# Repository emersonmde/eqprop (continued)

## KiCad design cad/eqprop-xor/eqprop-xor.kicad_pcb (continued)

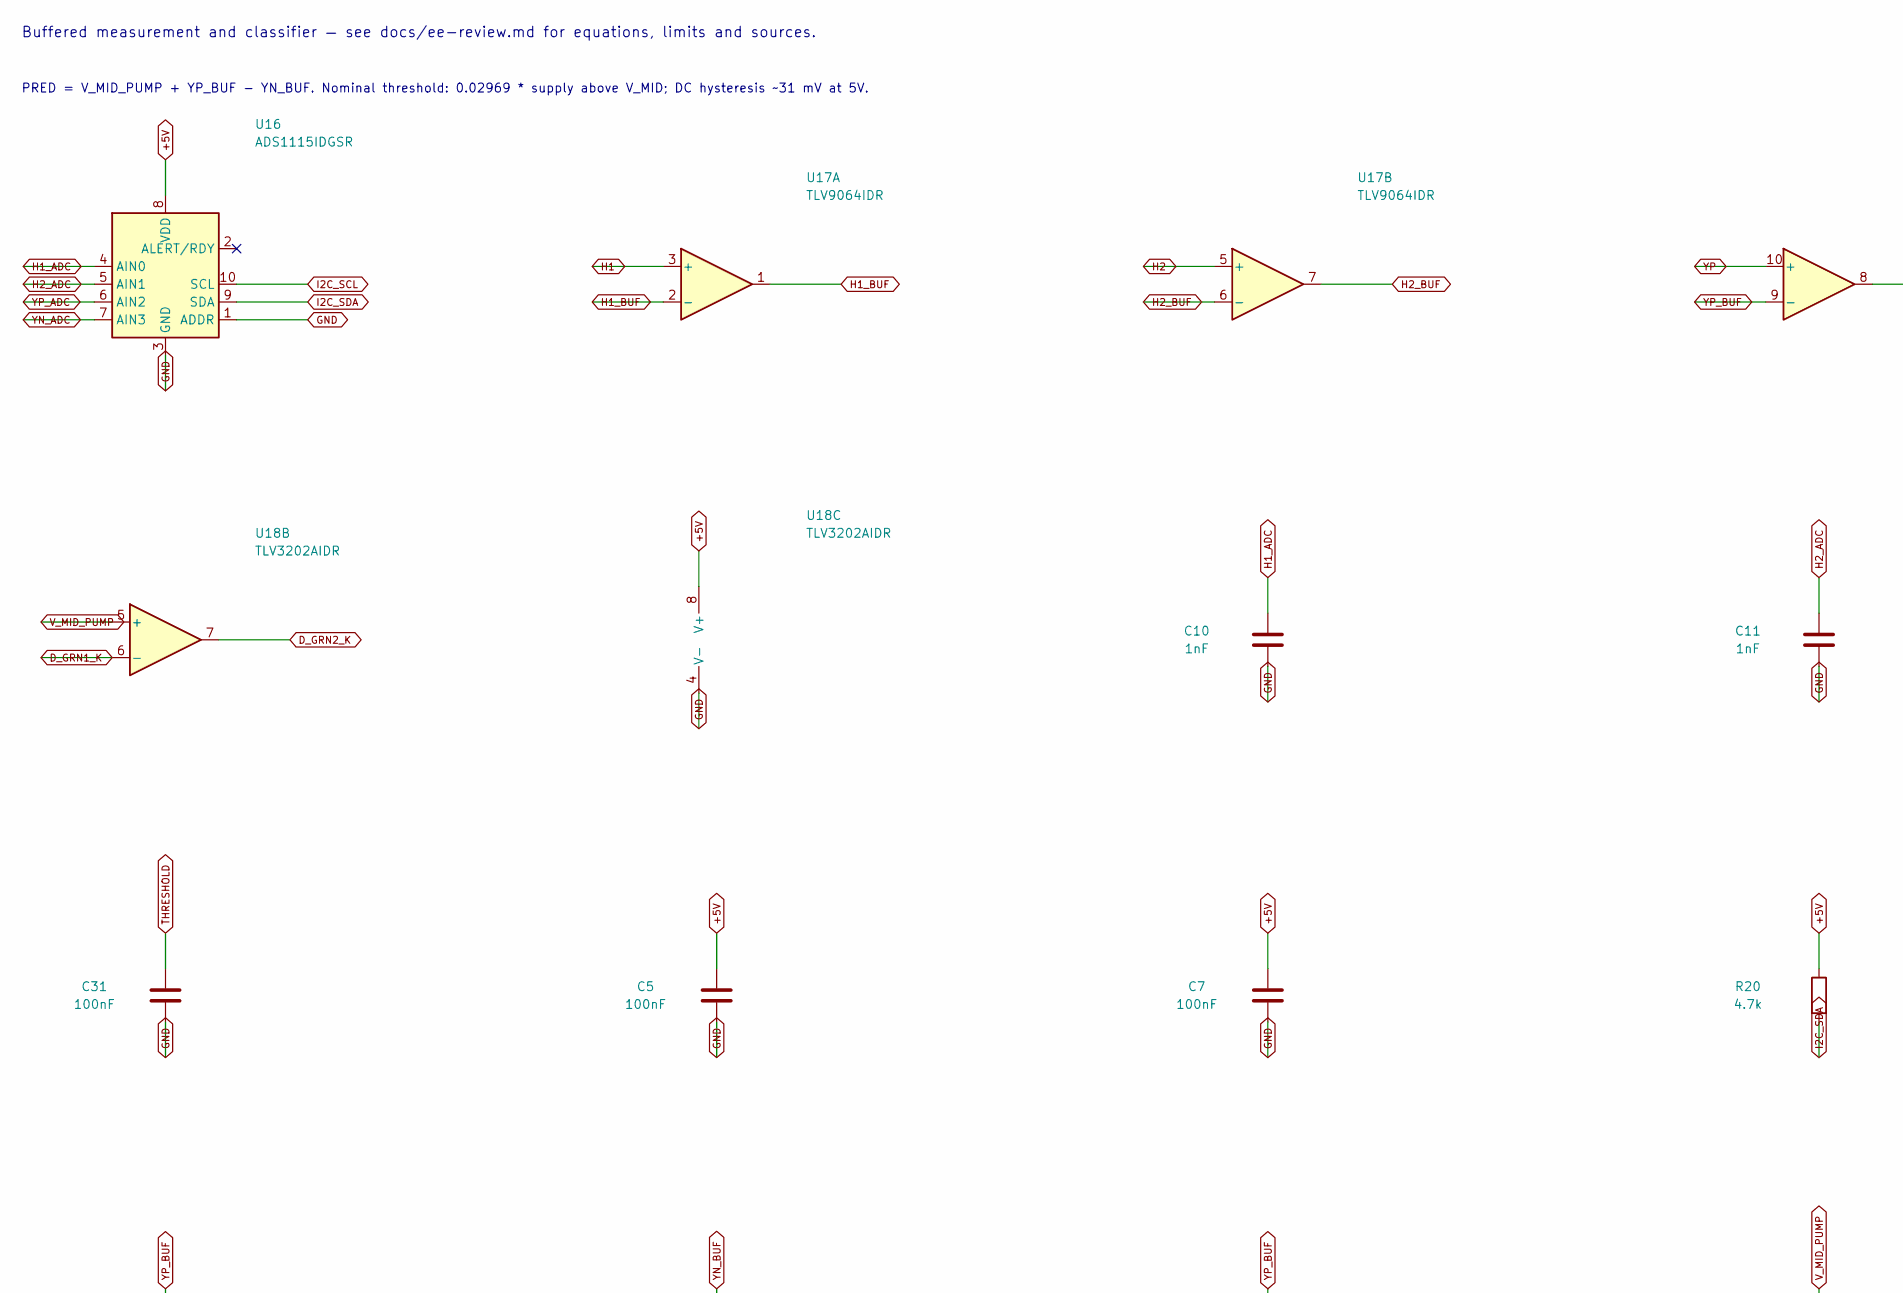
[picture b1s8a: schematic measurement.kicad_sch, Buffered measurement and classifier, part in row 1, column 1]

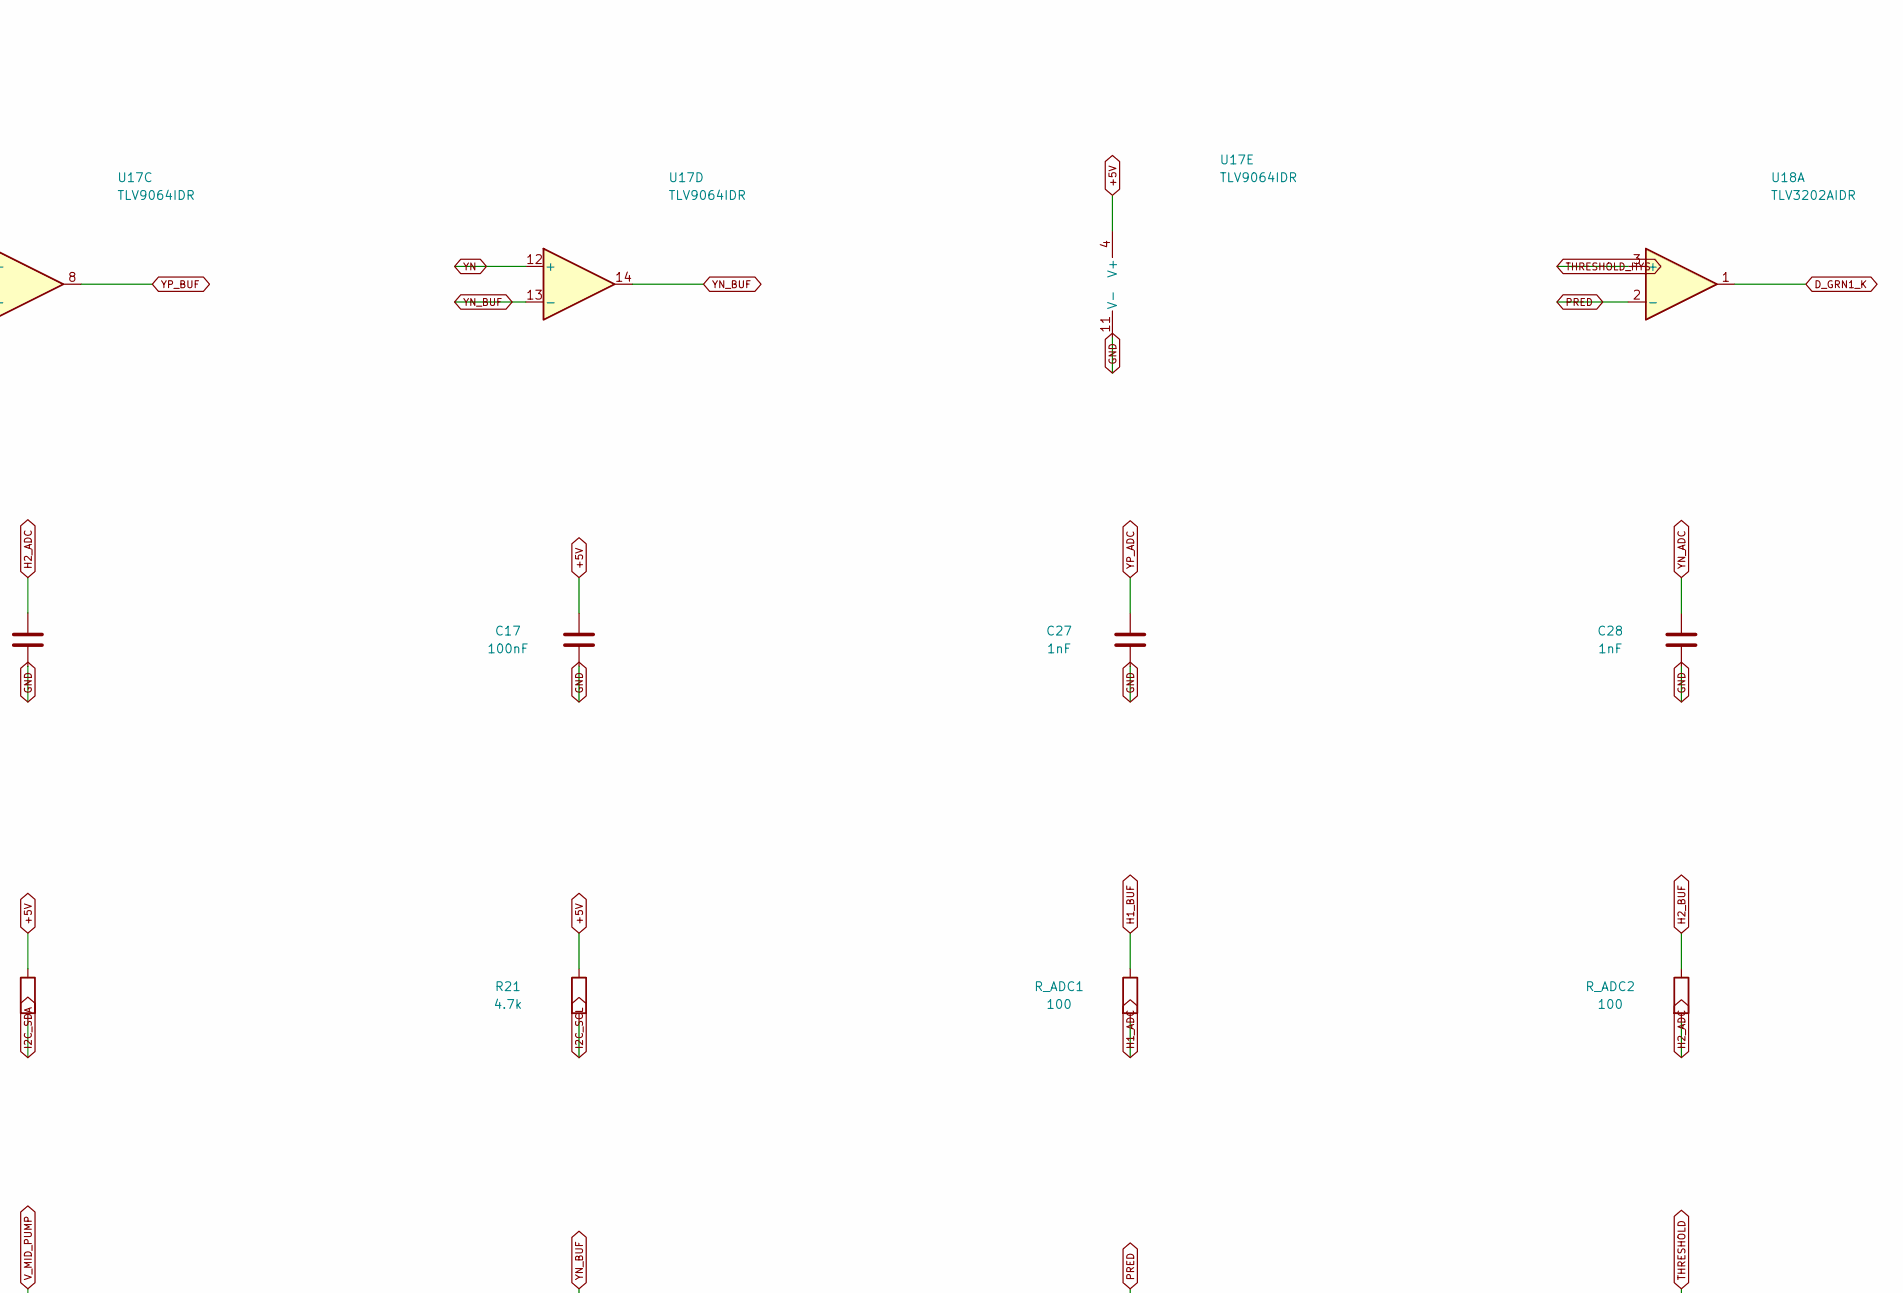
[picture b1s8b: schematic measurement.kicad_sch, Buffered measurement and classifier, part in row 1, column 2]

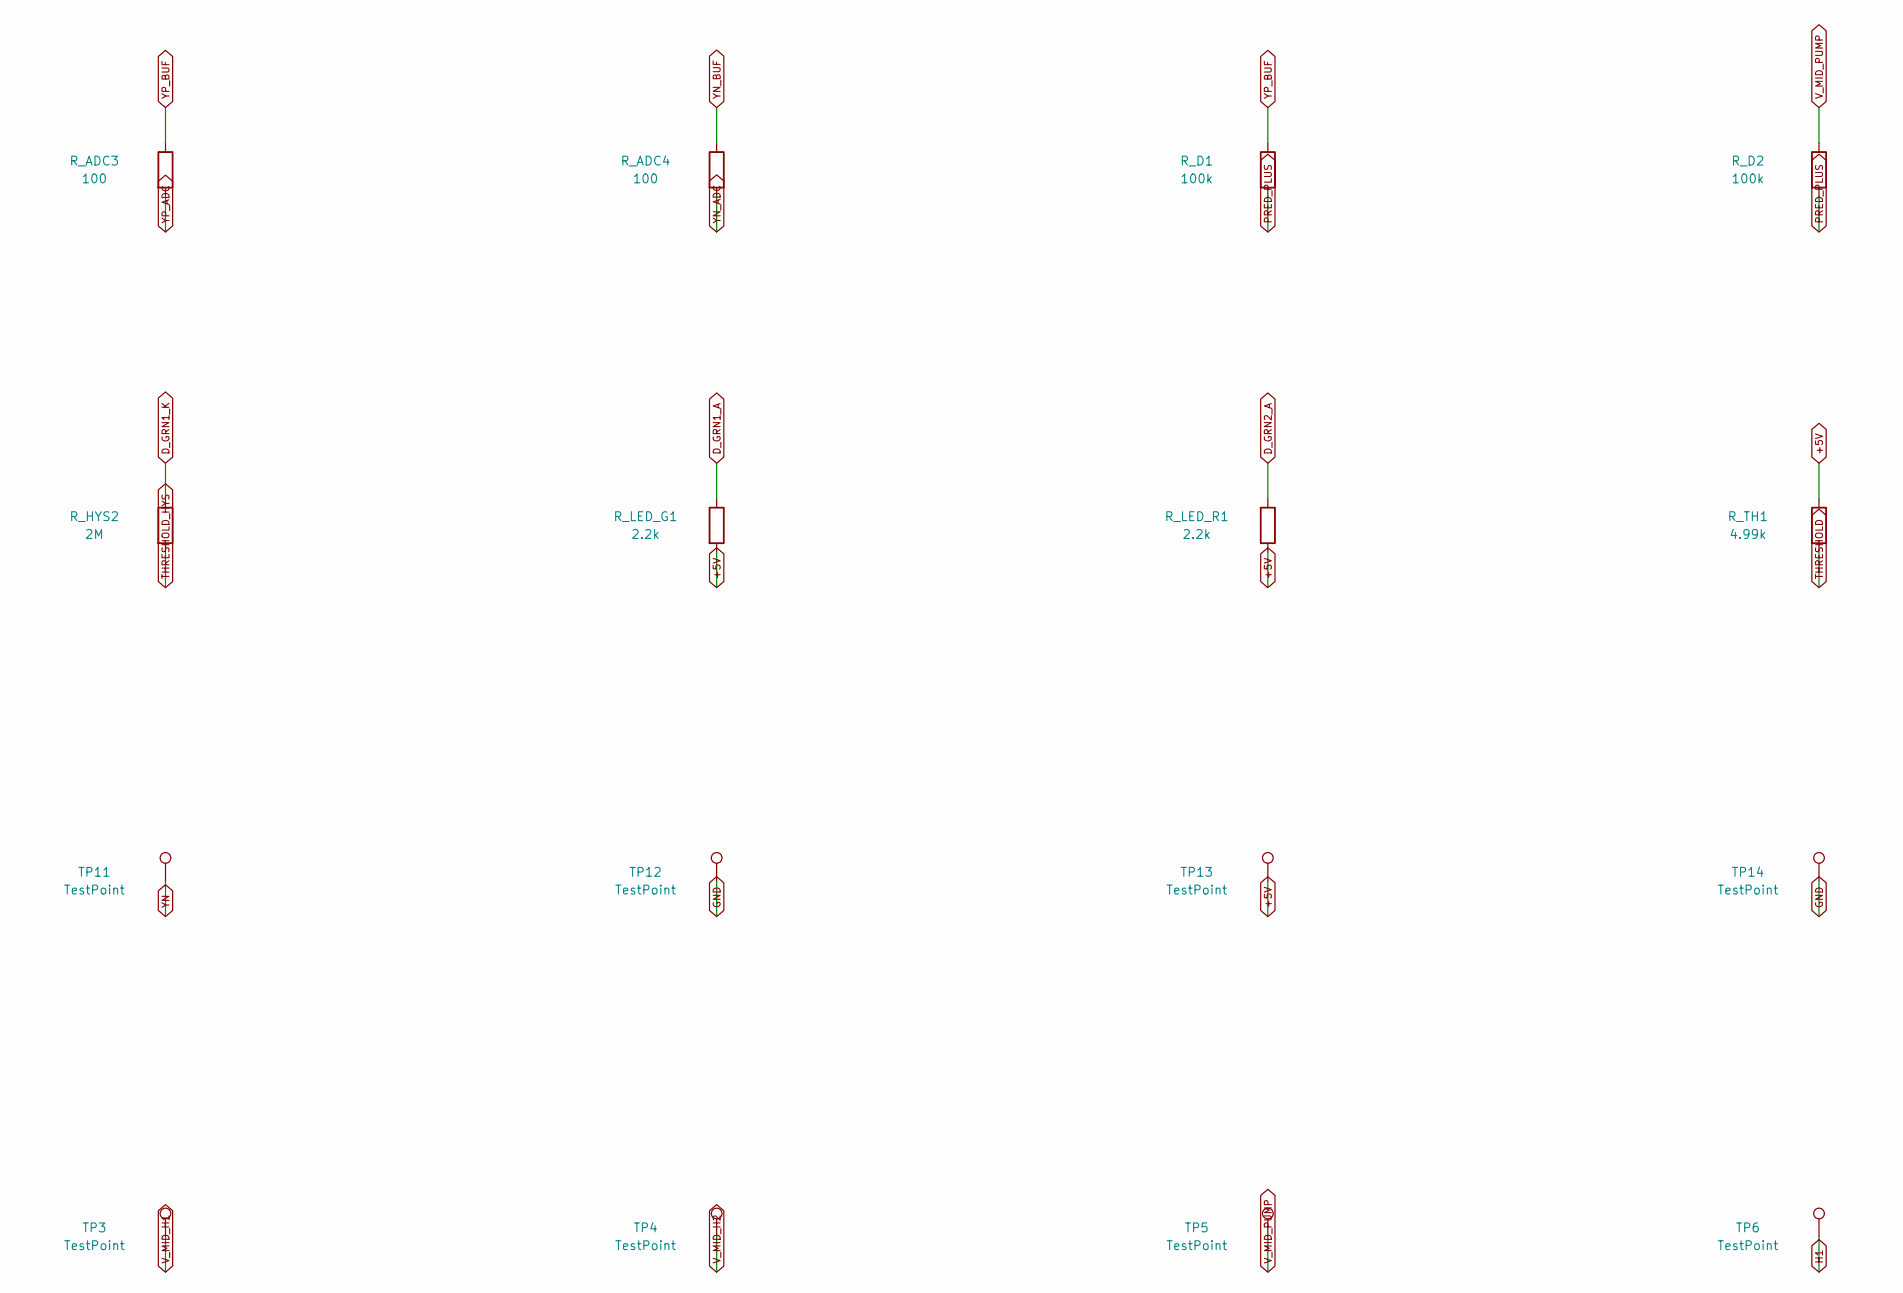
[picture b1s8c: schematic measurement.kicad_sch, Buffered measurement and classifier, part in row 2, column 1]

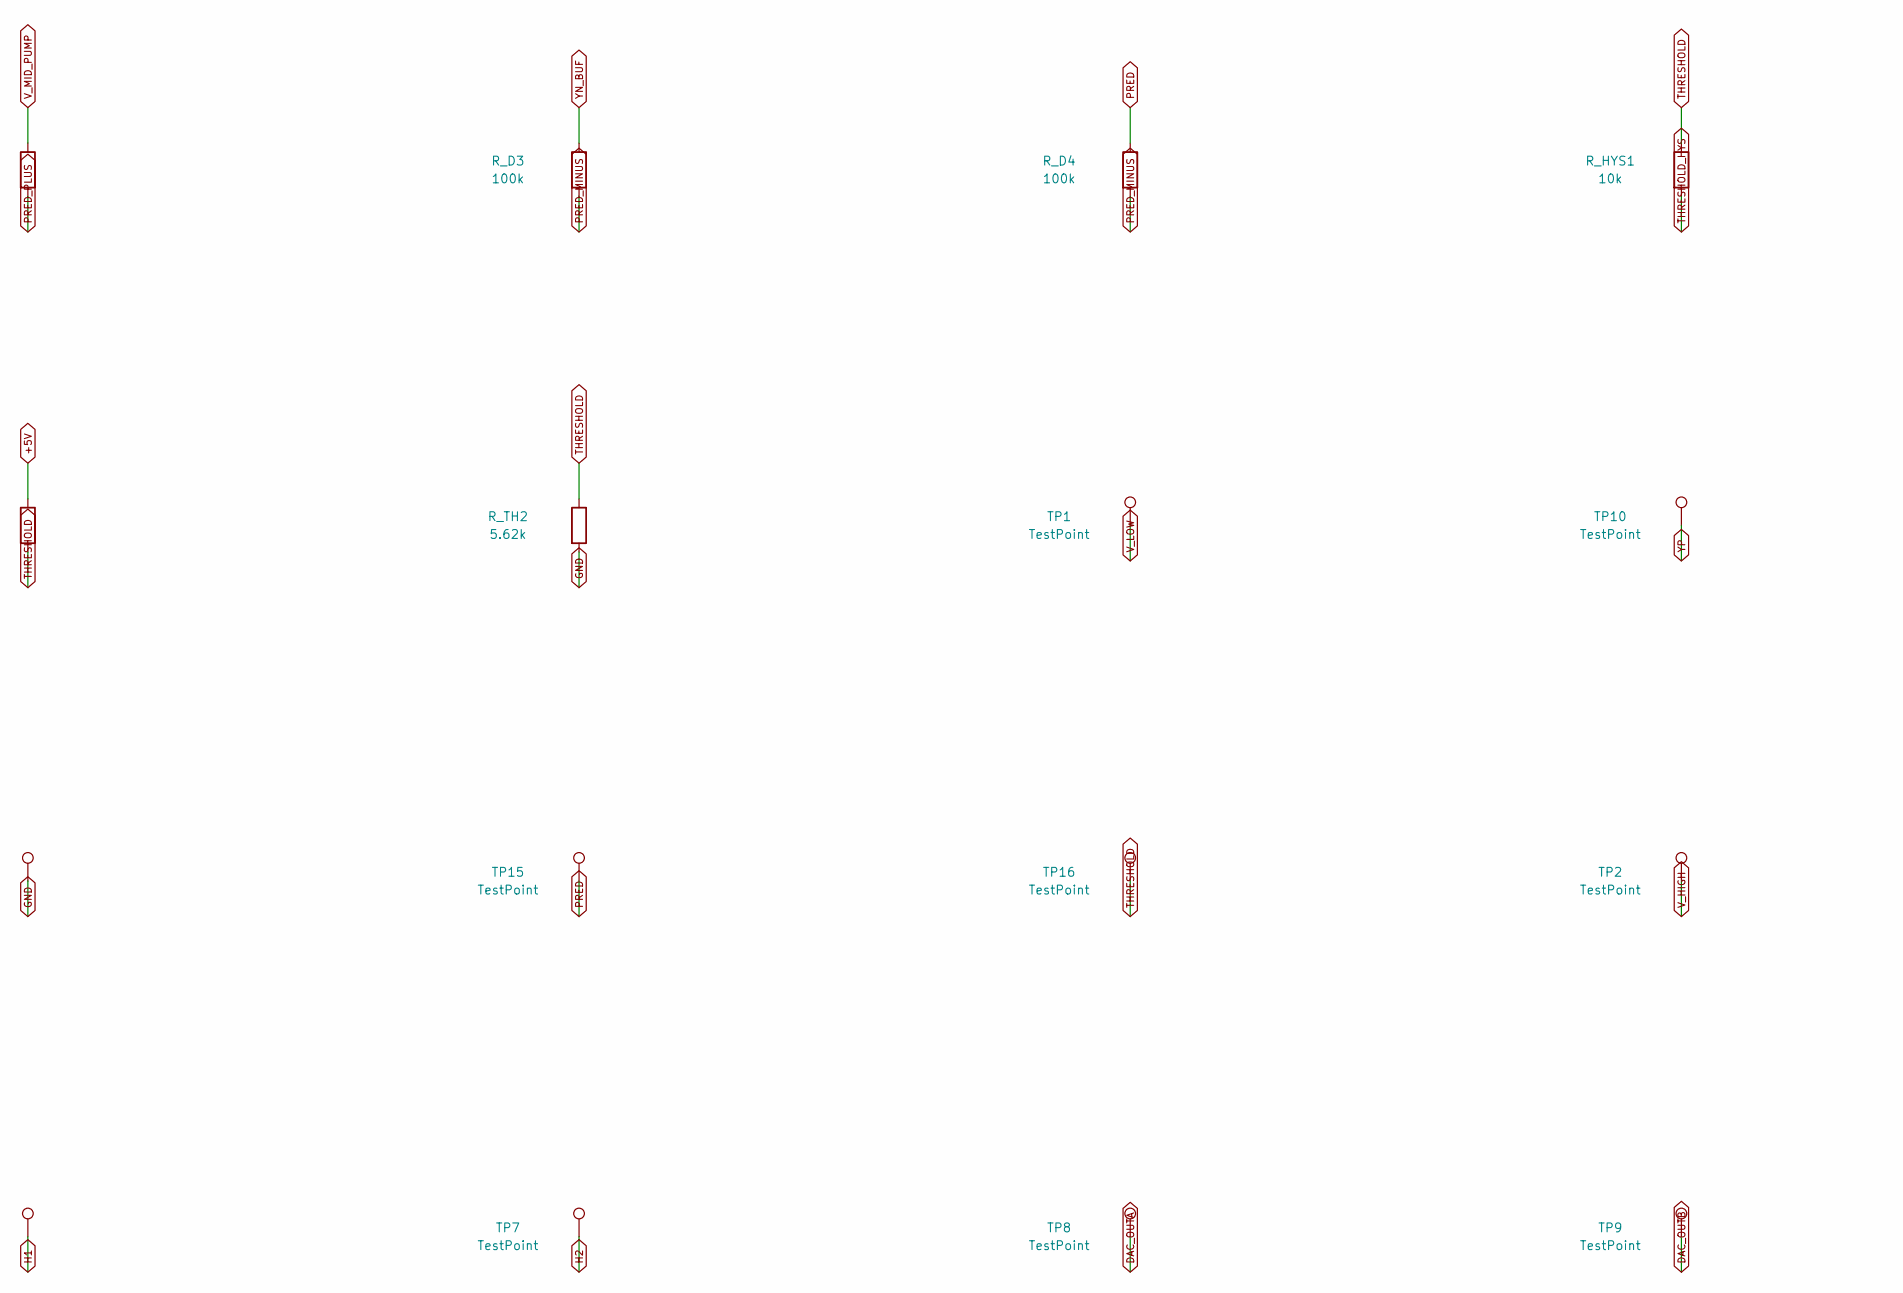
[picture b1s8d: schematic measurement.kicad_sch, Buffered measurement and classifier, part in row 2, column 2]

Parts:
C5, C7, C17, C31: 100nF; C_0805_2012Metric; MPN C0805C104K5RACTU
C10, C11, C27, C28: 1nF; C_0805_2012Metric; MPN C0805C102J5GACTU
R20, R21: 4.7k; R_0805_2012Metric; Tolerance 1%; MPN CRCW08054K70FKEA
R_ADC1, R_ADC2, R_ADC3, R_ADC4: 100; R_0805_2012Metric; Tolerance 1%; MPN CRCW0805100RFKEA
R_D1, R_D2, R_D3, R_D4: 100k; R_0805_2012Metric; Tolerance 0.1%; MPN TNPW0805100KBEEA
R_HYS1: 10k; R_0805_2012Metric; Tolerance 1%; MPN CRCW080510K0FKEA
R_HYS2: 2M; R_0805_2012Metric; Tolerance 1%; MPN CRCW08052M00FKEA
R_LED_G1: 2.2k; R_0805_2012Metric; Tolerance 1%; MPN CRCW08052K20FKEA
R_LED_R1: 2.2k; R_0805_2012Metric; Tolerance 1%; MPN CRCW08052K20FKEA
R_TH1: 4.99k; R_0805_2012Metric; Tolerance 0.1%; MPN TNPW08054K99BEEA
R_TH2: 5.62k; R_0805_2012Metric; Tolerance 0.1%; MPN TNPW08055K62BEEA
TP1, TP2, TP3, TP4, TP5, TP6, TP7, TP8, TP9, TP10, TP11, TP12, TP13, TP14, TP15, TP16: TestPoint; TestPoint_Pad_1.0x1.0mm; MPN PCB copper feature (no component)
U16: ADS1115IDGSR; TSSOP-10_3x3mm_P0.5mm; MPN ADS1115IDGSR
U17: TLV9064IDR; SOIC-14_3.9x8.7mm_P1.27mm; MPN TLV9064IDR
U18: TLV3202AIDR; SOIC-8_3.9x4.9mm_P1.27mm; MPN TLV3202AIDR

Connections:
+5V: C5.1, C7.1, C17.1, R20.1, R21.1, R_LED_G1.2, R_LED_R1.2, R_TH1.1, TP13.1, U16.8 (VDD), U17.4 (V+), U18.8 (V+); also elsewhere on the board
DAC_OUTA: TP8.1; also elsewhere on the board
DAC_OUTB: TP9.1; also elsewhere on the board
D_GRN1_A: R_LED_G1.1; also elsewhere on the board
D_GRN1_K: R_HYS2.1, U18.1, U18.6 (-); also elsewhere on the board
D_GRN2_A: R_LED_R1.1; also elsewhere on the board
D_GRN2_K: U18.7; also elsewhere on the board
GND: C5.2, C7.2, C10.2, C11.2, C17.2, C27.2, C28.2, C31.2, R_TH2.2, TP12.1, TP14.1, U16.1 (ADDR), U16.3 (GND), U17.11 (V-), U18.4 (V-); also elsewhere on the board
H1: TP6.1, U17.3 (+); also elsewhere on the board
H1_ADC: C10.1, R_ADC1.2, U16.4 (AIN0)
H1_BUF: R_ADC1.1, U17.1, U17.2 (-)
H2: TP7.1, U17.5 (+); also elsewhere on the board
H2_ADC: C11.1, R_ADC2.2, U16.5 (AIN1)
H2_BUF: R_ADC2.1, U17.6 (-), U17.7
I2C_SCL: R21.2, U16.10 (SCL); also elsewhere on the board
I2C_SDA: R20.2, U16.9 (SDA); also elsewhere on the board
PRED: R_D4.1, TP15.1, U18.2 (-); also elsewhere on the board
PRED_MINUS: R_D3.2, R_D4.2; also elsewhere on the board
PRED_PLUS: R_D1.2, R_D2.2; also elsewhere on the board
THRESHOLD: C31.1, R_HYS1.1, R_TH1.2, R_TH2.1, TP16.1
THRESHOLD_HYS: R_HYS1.2, R_HYS2.2, U18.3 (+)
V_HIGH: TP2.1; also elsewhere on the board
V_LOW: TP1.1; also elsewhere on the board
V_MID_H1: TP3.1; also elsewhere on the board
V_MID_H2: TP4.1; also elsewhere on the board
V_MID_PUMP: R_D2.1, TP5.1, U18.5 (+); also elsewhere on the board
YN: TP11.1, U17.12 (+); also elsewhere on the board
YN_ADC: C28.1, R_ADC4.2, U16.7 (AIN3)
YN_BUF: R_ADC4.1, R_D3.1, U17.13 (-), U17.14
YP: TP10.1, U17.10 (+); also elsewhere on the board
YP_ADC: C27.1, R_ADC3.2, U16.6 (AIN2)
YP_BUF: R_ADC3.1, R_D1.1, U17.8, U17.9 (-)

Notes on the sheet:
Buffered measurement and classifier — see docs/ee-review.md for equations, limits and sources.
PRED = V_MID_PUMP + YP_BUF - YN_BUF. Nominal threshold: 0.02969 * supply above V_MID; DC hysteresis ~31 mV at 5V.

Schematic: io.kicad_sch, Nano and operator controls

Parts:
D_GRN1, D_GRN2: Green low-current 3mm; LED_D3.0mm; MPN WP710A10LZGCK
D_PWR1: Green low-current 3mm; LED_D3.0mm; MPN WP710A10LZGCK
R_BUTTON1: 2.2k; R_0805_2012Metric; MPN CRCW08052K20FKEA
R_SW1, R_SW2: 10k; R_0805_2012Metric; Tolerance 1%; MPN CRCW080510K0FKEA
SW1, SW2: SW_SPDT; SW_E-Switch_EG1271_SPDT; MPN EG1271A
SW3: LEARN / STOP; SW_SPST_B3U-1000P; MPN B3U-1000P
U3: Arduino_Nano_v3.x; Arduino_Nano; MPN A000005

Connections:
+5V: R_BUTTON1.1, SW1.1 (A), SW2.1 (A), U3.27 (+5V); also elsewhere on the board
CS_DAC: U3.12 (D9); also elsewhere on the board
CS_POT1: U3.7 (D4); also elsewhere on the board
CS_POT2: U3.8 (D5); also elsewhere on the board
CS_POT3: U3.9 (D6); also elsewhere on the board
CS_POT4: U3.10 (D7); also elsewhere on the board
CS_POT5: U3.11 (D8); also elsewhere on the board
CS_POT6: U3.13 (D10); also elsewhere on the board
CS_POT7: U3.21 (A2); also elsewhere on the board
CS_POT8: U3.22 (A3); also elsewhere on the board
D_GRN1_A: D_GRN1.2 (A); also elsewhere on the board
D_GRN1_K: D_GRN1.1 (K); also elsewhere on the board
D_GRN2_A: D_GRN2.2 (A); also elsewhere on the board
D_GRN2_K: D_GRN2.1 (K); also elsewhere on the board
D_PWR1_A: D_PWR1.2 (A); also elsewhere on the board
GND: D_PWR1.1 (K), SW1.3 (C), SW2.3 (C), SW3.2, U3.4 (GND), U3.29 (GND); also elsewhere on the board
I2C_SCL: U3.24 (A5); also elsewhere on the board
I2C_SDA: U3.23 (A4); also elsewhere on the board
LEARN_BUTTON: R_BUTTON1.2, SW3.1, U3.25 (A6)
MUX_A: R_SW1.1, U3.5 (D2); also elsewhere on the board
MUX_B: R_SW2.1, U3.6 (D3); also elsewhere on the board
SPI_MISO: U3.15 (D12); also elsewhere on the board
SPI_MOSI: U3.14 (D11); also elsewhere on the board
SPI_SCK: U3.16 (D13); also elsewhere on the board
SW1_B: R_SW1.2, SW1.2 (B)
SW2_B: R_SW2.2, SW2.2 (B)
X1: U3.19 (A0); also elsewhere on the board
X2: U3.20 (A1); also elsewhere on the board

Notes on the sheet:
Nano and operator controls — see docs/ee-review.md for equations, limits and sources.
SW3: active-low A6 analog input; external pull-up required. Firmware: analogRead(A6), AVcc reference; debounce and act only at phase boundaries. B3U-1000P is NOT washable; assemble after any wet cleaning.

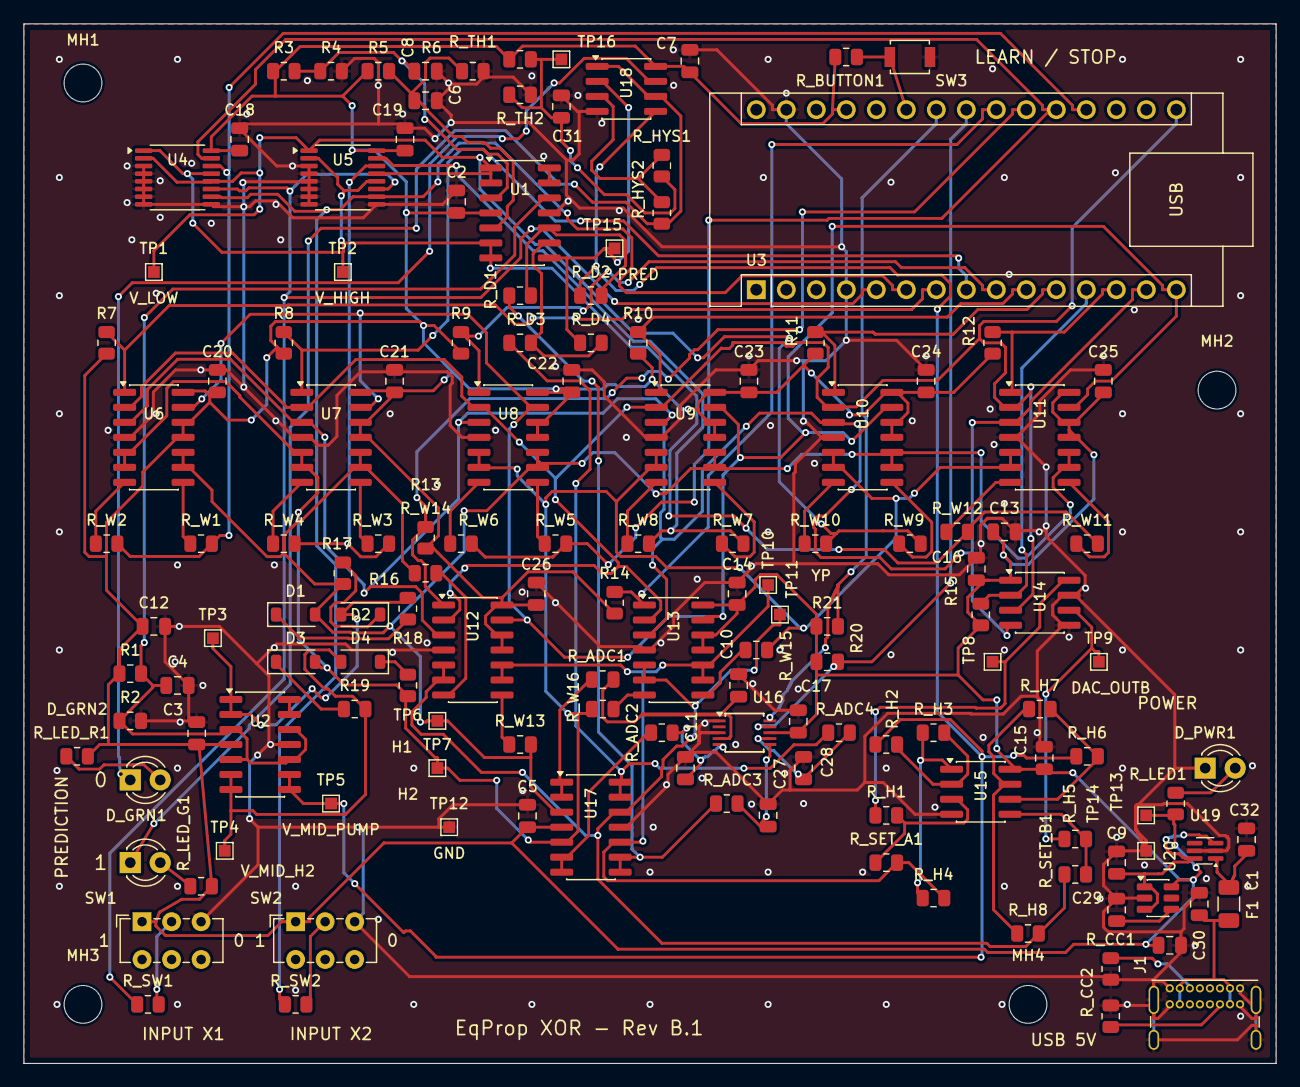
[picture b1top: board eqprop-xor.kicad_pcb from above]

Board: 2 copper layers, 106.0 x 88.0 mm, 151 parts (0 on the bottom side), 91 nets.

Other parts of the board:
MH1, MH2, MH3, MH4: M3; MountingHole_3.2mm_M3

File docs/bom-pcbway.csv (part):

References,Quantity,Value,Footprint,Manufacturer part number,Tolerance / rating,Datasheet,Assembly notes
C1,1,1uF,Capacitor_SMD:C_0805_2012Metric,C0805C105K4RACTU,"10%, X7R, 16V",https://search.kemet.com/component-documentation/download/sp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,Top-side SMD
C10,1,1nF,Capacitor_SMD:C_0805_2012Metric,C0805C102J5GACTU,"5%, C0G, 50V",https://search.kemet.com/component-documentation/download/sp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,Top-side SMD
C11,1,1nF,Capacitor_SMD:C_0805_2012Metric,C0805C102J5GACTU,"5%, C0G, 50V",https://search.kemet.com/component-documentation/download/sp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,Top-side SMD
C12,1,10uF,Capacitor_SMD:C_0805_2012Metric,C0805C106K8PACTU,"10%, X5R, 10V",https://search.kemet.com/component-documentation/download/sp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,Top-side SMD
C13,1,10uF,Capacitor_SMD:C_0805_2012Metric,C0805C106K8PACTU,"10%, X5R, 10V",https://search.kemet.com/component-documentation/download/sp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,Top-side SMD
C14,1,100nF,Capacitor_SMD:C_0805_2012Metric,C0805C104K5RACTU,"10%, X7R, 50V",https://search.kemet.com/component-documentation/download/sp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,Top-side SMD
C15,1,100nF,Capacitor_SMD:C_0805_2012Metric,C0805C104K5RACTU,"10%, X7R, 50V",https://search.kemet.com/component-documentation/download/sp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,Top-side SMD
C16,1,100nF,Capacitor_SMD:C_0805_2012Metric,C0805C104K5RACTU,"10%, X7R, 50V",https://search.kemet.com/component-documentation/download/sp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,Top-side SMD
C17,1,100nF,Capacitor_SMD:C_0805_2012Metric,C0805C104K5RACTU,"10%, X7R, 50V",https://search.kemet.com/component-documentation/download/sp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,Top-side SMD
C18,1,100nF,Capacitor_SMD:C_0805_2012Metric,C0805C104K5RACTU,"10%, X7R, 50V",https://search.kemet.com/component-documentation/download/sp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,Top-side SMD
C19,1,100nF,Capacitor_SMD:C_0805_2012Metric,C0805C104K5RACTU,"10%, X7R, 50V",https://search.kemet.com/component-documentation/download/sp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,Top-side SMD
C2,1,100nF,Capacitor_SMD:C_0805_2012Metric,C0805C104K5RACTU,"10%, X7R, 50V",https://search.kemet.com/component-documentation/download/sp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,Top-side SMD
C20,1,100nF,Capacitor_SMD:C_0805_2012Metric,C0805C104K5RACTU,"10%, X7R, 50V",https://search.kemet.com/component-documentation/download/sp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,Top-side SMD
C21,1,100nF,Capacitor_SMD:C_0805_2012Metric,C0805C104K5RACTU,"10%, X7R, 50V",https://search.kemet.com/component-documentation/download/sp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,Top-side SMD
C22,1,100nF,Capacitor_SMD:C_0805_2012Metric,C0805C104K5RACTU,"10%, X7R, 50V",https://search.kemet.com/component-documentation/download/sp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,Top-side SMD
C23,1,100nF,Capacitor_SMD:C_0805_2012Metric,C0805C104K5RACTU,"10%, X7R, 50V",https://search.kemet.com/component-documentation/download/sp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,Top-side SMD
C24,1,100nF,Capacitor_SMD:C_0805_2012Metric,C0805C104K5RACTU,"10%, X7R, 50V",https://search.kemet.com/component-documentation/download/sp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,Top-side SMD
C25,1,100nF,Capacitor_SMD:C_0805_2012Metric,C0805C104K5RACTU,"10%, X7R, 50V",https://search.kemet.com/component-documentation/download/sp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,Top-side SMD
C26,1,100nF,Capacitor_SMD:C_0805_2012Metric,C0805C104K5RACTU,"10%, X7R, 50V",https://search.kemet.com/component-documentation/download/sp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,Top-side SMD
C27,1,1nF,Capacitor_SMD:C_0805_2012Metric,C0805C102J5GACTU,"5%, C0G, 50V",https://search.kemet.com/component-documentation/download/sp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,Top-side SMD
C28,1,1nF,Capacitor_SMD:C_0805_2012Metric,C0805C102J5GACTU,"5%, C0G, 50V",https://search.kemet.com/component-documentation/download/sp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,Top-side SMD
C29,1,10nF,Capacitor_SMD:C_0805_2012Metric,C0805C103K5RACTU,"10%, X7R, 50V",https://search.kemet.com/component-documentation/download/sp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,Top-side SMD
C3,1,100nF,Capacitor_SMD:C_0805_2012Metric,C0805C104K5RACTU,"10%, X7R, 50V",https://search.kemet.com/component-documentation/download/sp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,Top-side SMD
C30,1,10uF,Capacitor_SMD:C_0805_2012Metric,C0805C106K8PACTU,"10%, X5R, 10V",https://search.kemet.com/component-documentation/download/sp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,Top-side SMD
C31,1,100nF,Capacitor_SMD:C_0805_2012Metric,C0805C104K5RACTU,"10%, X7R, 50V",https://search.kemet.com/component-documentation/download/sp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,Top-side SMD
C32,1,1uF,Capacitor_SMD:C_0805_2012Metric,C0805C105K4RACTU,"10%, X7R, 16V",https://search.kemet.com/component-documentation/download/sp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,Top-side SMD
C4,1,1uF,Capacitor_SMD:C_0805_2012Metric,C0805C105K4RACTU,"10%, X7R, 16V",https://search.kemet.com/component-documentation/download/sp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,Top-side SMD
C5,1,100nF,Capacitor_SMD:C_0805_2012Metric,C0805C104K5RACTU,"10%, X7R, 50V",https://search.kemet.com/component-documentation/download/sp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,Top-side SMD
C6,1,1uF,Capacitor_SMD:C_0805_2012Metric,C0805C105K4RACTU,"10%, X7R, 16V",https://search.kemet.com/component-documentation/download/sp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,Top-side SMD
C7,1,100nF,Capacitor_SMD:C_0805_2012Metric,C0805C104K5RACTU,"10%, X7R, 50V",https://search.kemet.com/component-documentation/download/sp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,Top-side SMD
C8,1,1uF,Capacitor_SMD:C_0805_2012Metric,C0805C105K4RACTU,"10%, X7R, 16V",https://search.kemet.com/component-documentation/download/sp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,Top-side SMD
C9,1,1uF,Capacitor_SMD:C_0805_2012Metric,C0805C105K4RACTU,"10%, X7R, 16V",https://search.kemet.com/component-documentation/download/sp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,Top-side SMD
D1,1,BAT42W-G3-08,Diode_SMD:D_SOD-123,BAT42W-G3-08,,https://www.vishay.com/docs/86405/bat42w-g.pdf,Top-side SMD
D2,1,BAT42W-G3-08,Diode_SMD:D_SOD-123,BAT42W-G3-08,,https://www.vishay.com/docs/86405/bat42w-g.pdf,Top-side SMD
D3,1,BAT42W-G3-08,Diode_SMD:D_SOD-123,BAT42W-G3-08,,https://www.vishay.com/docs/86405/bat42w-g.pdf,Top-side SMD
D4,1,BAT42W-G3-08,Diode_SMD:D_SOD-123,BAT42W-G3-08,,https://www.vishay.com/docs/86405/bat42w-g.pdf,Top-side SMD
D_GRN1,1,Green low-current 3mm,LED_THT:LED_D3.0mm,WP710A10LZGCK,,https://www.kingbrightusa.com/images/catalog/SPEC/WP710A10LZGCK.pdf,Through-hole assembly
D_GRN2,1,Green low-current 3mm,LED_THT:LED_D3.0mm,WP710A10LZGCK,,https://www.kingbrightusa.com/images/catalog/SPEC/WP710A10LZGCK.pdf,Through-hole assembly
D_PWR1,1,Green low-current 3mm,LED_THT:LED_D3.0mm,WP710A10LZGCK,,https://www.kingbrightusa.com/images/catalog/SPEC/WP710A10LZGCK.pdf,Through-hole assembly
F1,1,250mA PTC,Fuse:Fuse_1206_3216Metric,MF-NSMF025X-2,,https://www.bourns.com/docs/product-datasheets/mf-nsmf.pdf,Top-side SMD
J1,1,USB_C_Receptacle_USB2.0_14P,EqProp:USB4085_Edge,USB4085-GF-A,,https://gct.co/connector/usb4085,Through-hole assembly
R1,1,10k,Resistor_SMD:R_0805_2012Metric,TNPW080510K0BEEA,0.1%; 0.125 W minimum; 25 ppm/K,https://www.vishay.com/docs/28758/tnpw_e3.pdf,Top-side SMD
R10,1,10k,Resistor_SMD:R_0805_2012Metric,CRCW080510K0FKEA,1%; 0.125 W; 100 ppm/K,https://www.vishay.com/docs/20035/dcrcwe3.pdf,Top-side SMD
R11,1,10k,Resistor_SMD:R_0805_2012Metric,CRCW080510K0FKEA,1%; 0.125 W; 100 ppm/K,https://www.vishay.com/docs/20035/dcrcwe3.pdf,Top-side SMD
R12,1,10k,Resistor_SMD:R_0805_2012Metric,CRCW080510K0FKEA,1%; 0.125 W; 100 ppm/K,https://www.vishay.com/docs/20035/dcrcwe3.pdf,Top-side SMD
R13,1,10k,Resistor_SMD:R_0805_2012Metric,CRCW080510K0FKEA,1%; 0.125 W; 100 ppm/K,https://www.vishay.com/docs/20035/dcrcwe3.pdf,Top-side SMD
R14,1,10k,Resistor_SMD:R_0805_2012Metric,CRCW080510K0FKEA,1%; 0.125 W; 100 ppm/K,https://www.vishay.com/docs/20035/dcrcwe3.pdf,Top-side SMD
R15,1,10k,Resistor_SMD:R_0805_2012Metric,CRCW080510K0FKEA,1%; 0.125 W; 100 ppm/K,https://www.vishay.com/docs/20035/dcrcwe3.pdf,Top-side SMD
R16,1,0,Resistor_SMD:R_0805_2012Metric,CRCW08050000Z0EA,Jumper; 0 ohm jumper; see manufacturer current rating,https://www.vishay.com/docs/20035/dcrcwe3.pdf,Top-side SMD
R17,1,0,Resistor_SMD:R_0805_2012Metric,CRCW08050000Z0EA,Jumper; 0 ohm jumper; see manufacturer current rating,https://www.vishay.com/docs/20035/dcrcwe3.pdf,Top-side SMD
R18,1,0,Resistor_SMD:R_0805_2012Metric,CRCW08050000Z0EA,Jumper; 0 ohm jumper; see manufacturer current rating,https://www.vishay.com/docs/20035/dcrcwe3.pdf,Top-side SMD
R19,1,0,Resistor_SMD:R_0805_2012Metric,CRCW08050000Z0EA,Jumper; 0 ohm jumper; see manufacturer current rating,https://www.vishay.com/docs/20035/dcrcwe3.pdf,Top-side SMD
R2,1,10k,Resistor_SMD:R_0805_2012Metric,TNPW080510K0BEEA,0.1%; 0.125 W minimum; 25 ppm/K,https://www.vishay.com/docs/28758/tnpw_e3.pdf,Top-side SMD
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
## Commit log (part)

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2026-02-18 Added schematic snapshot image
2026-02-27 Started PCB design
